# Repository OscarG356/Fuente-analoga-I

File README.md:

# Fuente-analoga-I

Dentro de la carpeta "Fuente_Analoga" existe un archivo llamado "Materiales.csv" que contiene un listado de elementos requeridos para realizar la fuente.
También se incluye un esquematico para el uso de un ardunio nano.

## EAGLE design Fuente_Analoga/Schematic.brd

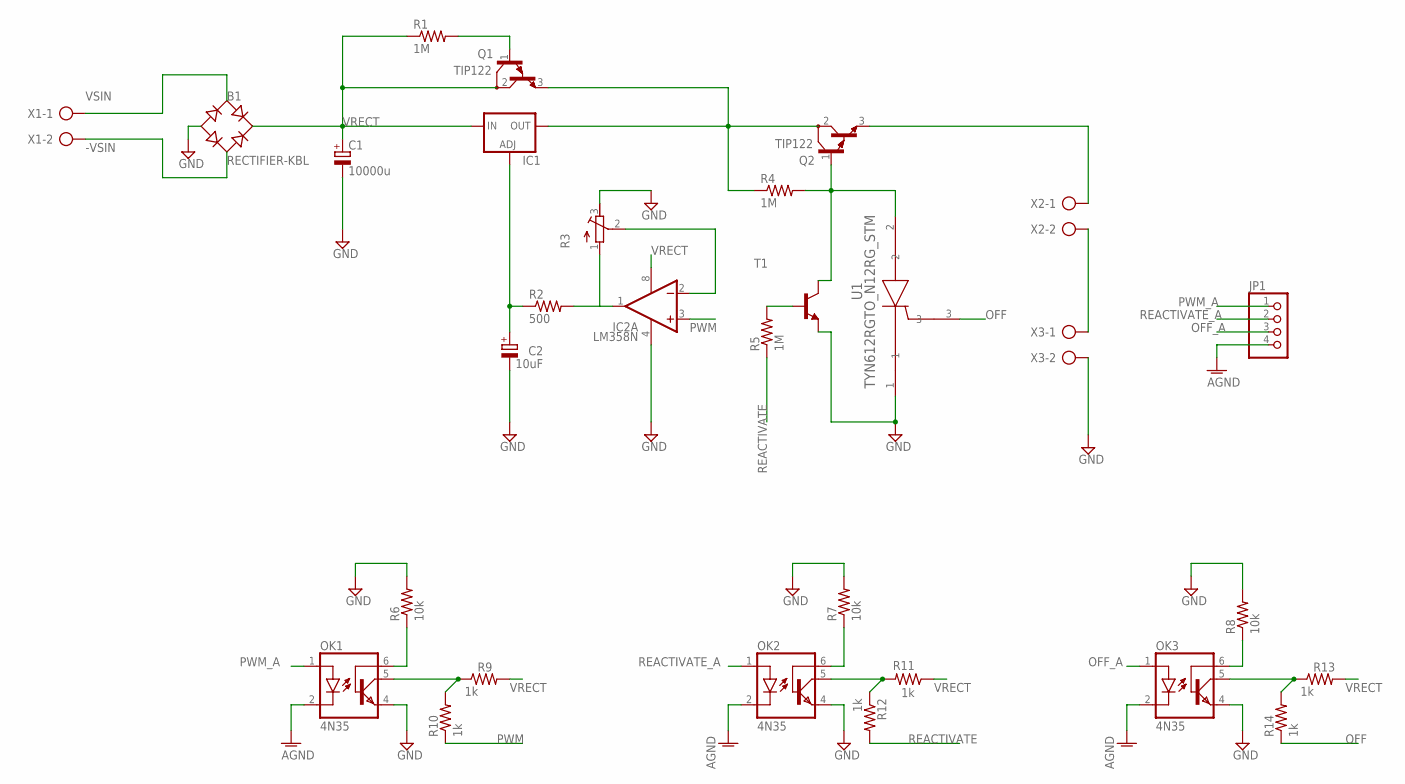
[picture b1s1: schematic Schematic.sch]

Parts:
B1: RECTIFIER-KBL; KBL
C1: 10000u; EB35D
C2: 10uF; E2-5
IC1: LM317TS; 317TS
IC2: LM358N; DIL08
JP1: PINHD-1X4; 1X04
OK1, OK2, OK3: 4N35; DIL06
Q1, Q2: TIP122; TO220
R1, R4, R5: 1M; 0207/10
R2: 500; 0207/10
R3: R-TRIMM64W; RTRIM64W
R6, R7, R8: 10k; 0207/10
R9, R10, R11, R12, R13, R14: 1k; 0204/7
T1: 2N2222-NPN-TO92-EBC; TO92-EBC
U1: TYN612RGTO_N12RG_STM; TO_N12RG_STM
X1, X2, X3: AK500/2

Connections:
-VSIN: B1.AC2, X1.2
AGND: OK1.2 (C), OK2.2 (C), OK3.2 (C)
GND: B1.-, C1.-, C2.-, IC2.4 (V-), JP1.4, OK1.4 (EMI), OK2.4 (EMI), OK3.4 (EMI), R3.3 (E), R6.2, R7.2, R8.2, T1.E, U1.1, X3.2
unnamed: IC2.2 (-IN), R3.2 (S)
unnamed: R5.2, T1.B
unnamed: IC2.1 (OUT), R2.2, R3.1 (A)
unnamed: Q1.1 (B), R1.2
unnamed: C2.+, IC1.1 (ADJ), R2.1
unnamed: IC1.2 (OUT), Q1.3 (E), Q2.2 (C), R4.1
unnamed: OK1.6 (BAS), R6.1
unnamed: Q2.1 (B), R4.2, T1.C, U1.2
unnamed: Q2.3 (E), X2.1
unnamed: X2.2, X3.1
unnamed: OK3.5 (COL), R13.1, R14.2
unnamed: OK2.6 (BAS), R7.1
unnamed: OK2.5 (COL), R11.2, R12.1
unnamed: OK3.6 (BAS), R8.1
unnamed: OK1.5 (COL), R9.1, R10.2
OFF: R14.1, U1.3
OFF_A: JP1.3, OK3.1 (A)
PWM: IC2.3 (+IN), R10.1
PWM_A: JP1.1, OK1.1 (A)
REACTIVATE: R5.1, R12.2
REACTIVATE_A: JP1.2, OK2.1 (A)
VRECT: B1.+, C1.+, IC1.3 (IN), IC2.8 (V+), Q1.2 (C), R1.1, R9.2, R11.1, R13.2
VSIN: B1.AC1, X1.1

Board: 2 copper layers, 30 parts (0 on the bottom side), 26 nets, no tracks yet.

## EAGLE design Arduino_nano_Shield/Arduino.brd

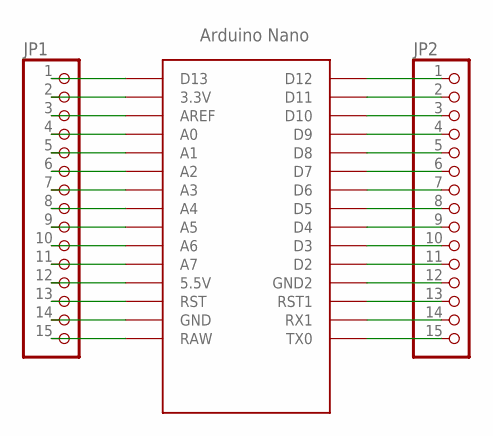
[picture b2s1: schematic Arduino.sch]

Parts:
JP1, JP2: PINHD-1X15; 1X15
U$1: NANO

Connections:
unnamed: JP1.1, U$1.D13
unnamed: JP1.2, U$1.3.3V
unnamed: JP1.3, U$1.AREF
unnamed: JP1.4, U$1.A0
unnamed: JP1.5, U$1.A1
unnamed: JP1.6, U$1.A2
unnamed: JP1.7, U$1.A3
unnamed: JP1.8, U$1.A4
unnamed: JP1.9, U$1.A5
unnamed: JP1.10, U$1.A6
unnamed: JP1.11, U$1.A7
unnamed: JP1.12, U$1.5V (5.5V)
unnamed: JP1.13, U$1.RST
unnamed: JP1.14, U$1.GND
unnamed: JP1.15, U$1.RAW
unnamed: JP2.1, U$1.D12
unnamed: JP2.2, U$1.D11
unnamed: JP2.3, U$1.D10
unnamed: JP2.4, U$1.D9
unnamed: JP2.5, U$1.D8
unnamed: JP2.6, U$1.D7
unnamed: JP2.7, U$1.D6
unnamed: JP2.8, U$1.D5
unnamed: JP2.9, U$1.D4
unnamed: JP2.10, U$1.D3
unnamed: JP2.11, U$1.D2
unnamed: JP2.12, U$1.GND1 (GND2)
unnamed: JP2.13, U$1.RST1
unnamed: JP2.14, U$1.RX1
unnamed: JP2.15, U$1.TX0

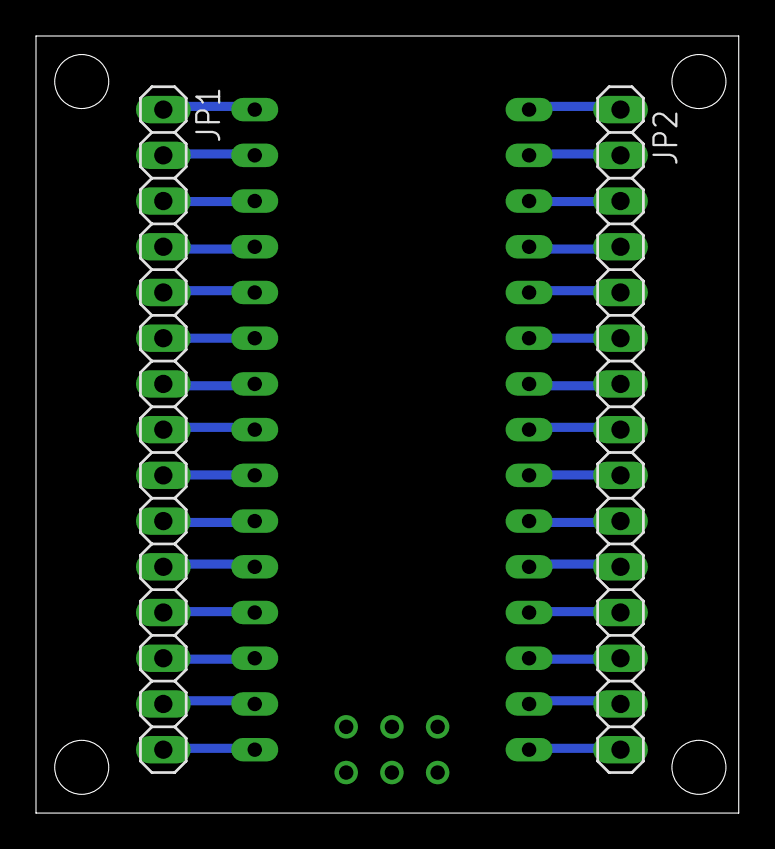
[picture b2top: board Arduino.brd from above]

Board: 2 copper layers, 39.0 x 43.2 mm, 3 parts (0 on the bottom side), 30 nets.

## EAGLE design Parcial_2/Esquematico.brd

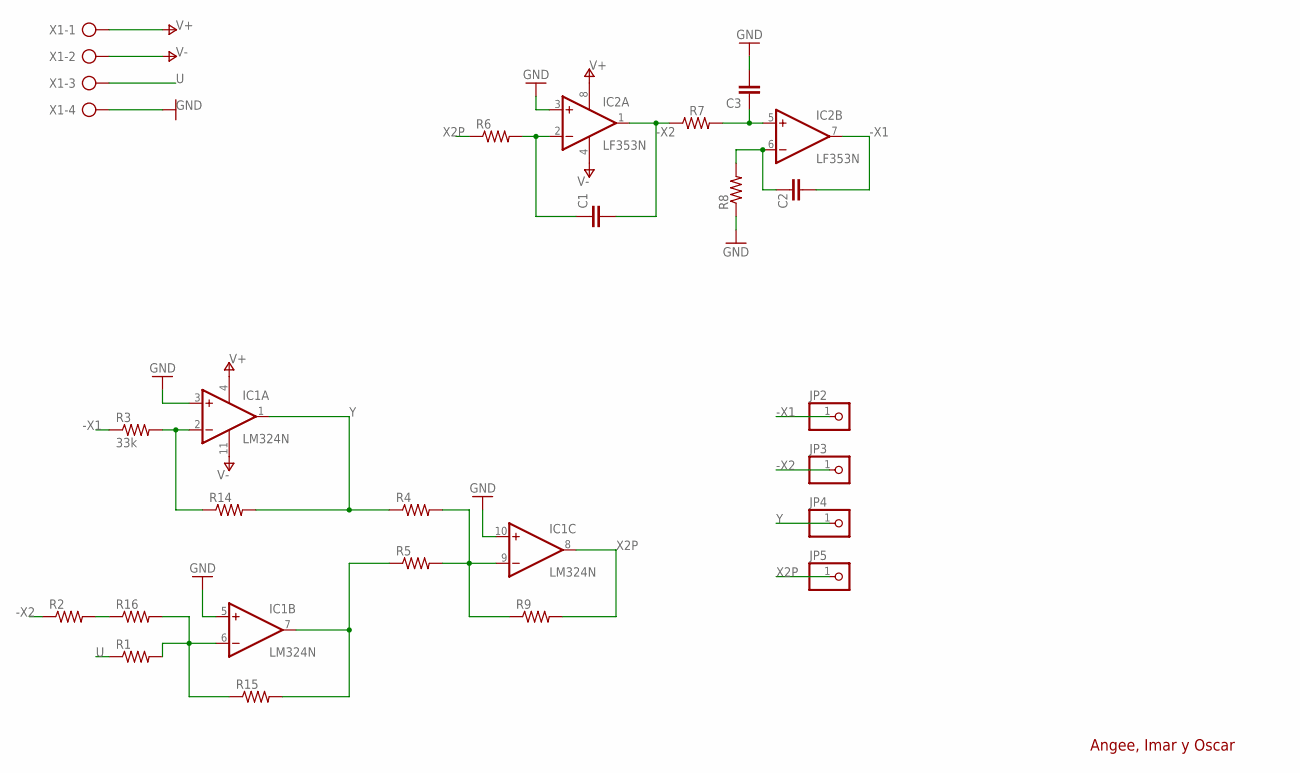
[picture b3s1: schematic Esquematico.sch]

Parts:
C1, C2, C3: C-EU150-054X183; C150-054X183
IC1: LM324N; DIL14
IC2: LF353N; DIL08
JP2, JP3, JP4, JP5: PINHD-1X1; 1X01
R1, R2, R4, R5, R6, R7, R8, R9, R14, R15, R16: R-US_0204/7; 0204/7
R3: 33k; 0204/7
X1: AK300/4

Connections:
-X1: C2.2, IC2.7 (OUT), JP2.1, R3.1
-X2: C1.2, IC2.1 (OUT), JP3.1, R2.1, R7.1
GND: C3.2, IC1.3 (+IN), IC1.5 (+IN), IC1.10 (+IN), IC2.3 (+IN), R8.1, X1.4
unnamed: R2.2, R16.1
unnamed: C1.1, IC2.2 (-IN), R6.2
unnamed: C2.1, IC2.6 (-IN), R8.2
unnamed: C3.1, IC2.5 (+IN), R7.2
unnamed: IC1.6 (-IN), R1.2, R15.1, R16.2
unnamed: IC1.2 (-IN), R3.2, R14.1
unnamed: IC1.7 (OUT), R5.1, R15.2
unnamed: IC1.9 (-IN), R4.2, R5.2, R9.1
U: R1.1, X1.3
V+: IC1.4 (V+), IC2.8 (V+), X1.1
V-: IC1.11 (V-), IC2.4 (V-), X1.2
X2P: IC1.8 (OUT), JP5.1, R6.1, R9.2
Y: IC1.1 (OUT), JP4.1, R4.1, R14.2

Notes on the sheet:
Angee, Imar y Oscar

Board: 2 copper layers, 22 parts (0 on the bottom side), 16 nets, no tracks yet.

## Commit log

2024-05-01 Creación del esquematico eagle
2024-05-02 Intento :c
2024-06-10 Se añaden los archivos de eagle del proyecto

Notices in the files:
parts and their libraries:
COPYRIGHT: Copyright (C) 2024 Ultra Librarian. All rights reserved.
